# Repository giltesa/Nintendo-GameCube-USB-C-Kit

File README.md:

# Nintendo GameCube: USB-C Kit

The **Nintendo GameCube: USB-C Kit** is a board that allows to replace the original power connector for a modern and standard USB-C.

**If your original connector / power supply is too old or damaged** and you need a new one, or **if you would like to power up your Nintendo GameCube with a standard USB-C PD charger**, such as the charger for your phone, or laptop, you can do so with this kit.

## HOW DOES IT WORK?

The **USB-C Power Delivery technology (USB-C PD)** allows for communication between the device and the charger, enabling the negotiation of the voltage to be supplied through the USB-C cable. In this case, the microchip included in this board is configured to request 12V, signaling to the charger that it requires 12V to operate. If the charger is compatible, it will supply the requested voltage. If it’s not compatible, nothing will happen, and the Nintendo GameCube won’t be able to power on.

## Would you like it?

[**Nintendo GameCube: USB-C Kit**](https://shop.giltesa.com/?p=1995)

## License

This project is licensed under a **Creative Commons** license:
**[Attribution-NonCommercial-ShareAlike 4.0 International (CC BY-NC-SA 4.0) ](https://creativecommons.org/licenses/by-nc-sa/4.0/)**

Check the [LICENSE.md](LICENSE.md) for more information.

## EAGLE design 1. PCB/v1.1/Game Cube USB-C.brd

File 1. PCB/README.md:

# Source Code Availability Notice

The source code for the electronic circuits previously shared in this repository is **no longer publicly available**.

This decision has been made due to repeated misuse of the shared materials by third parties who have used the code to manufacture and sell products derived from this work for commercial gain, in violation of the license under which it was originally shared.

The original license explicitly **prohibits commercial use** of this work without proper authorization. Unfortunately, the terms of the license were not respected, which undermines the purpose of sharing the source code and the trust of the community.

Thank you for your understanding and respect for intellectual property rights.

## Unauthorized Sellers

The following vendors are listed here because they have **violated the project license** and are **illegally profiting** from the sale of counterfeit products without our authorization:

- Treasure Game Accessory Store

- Shop910920001 Store

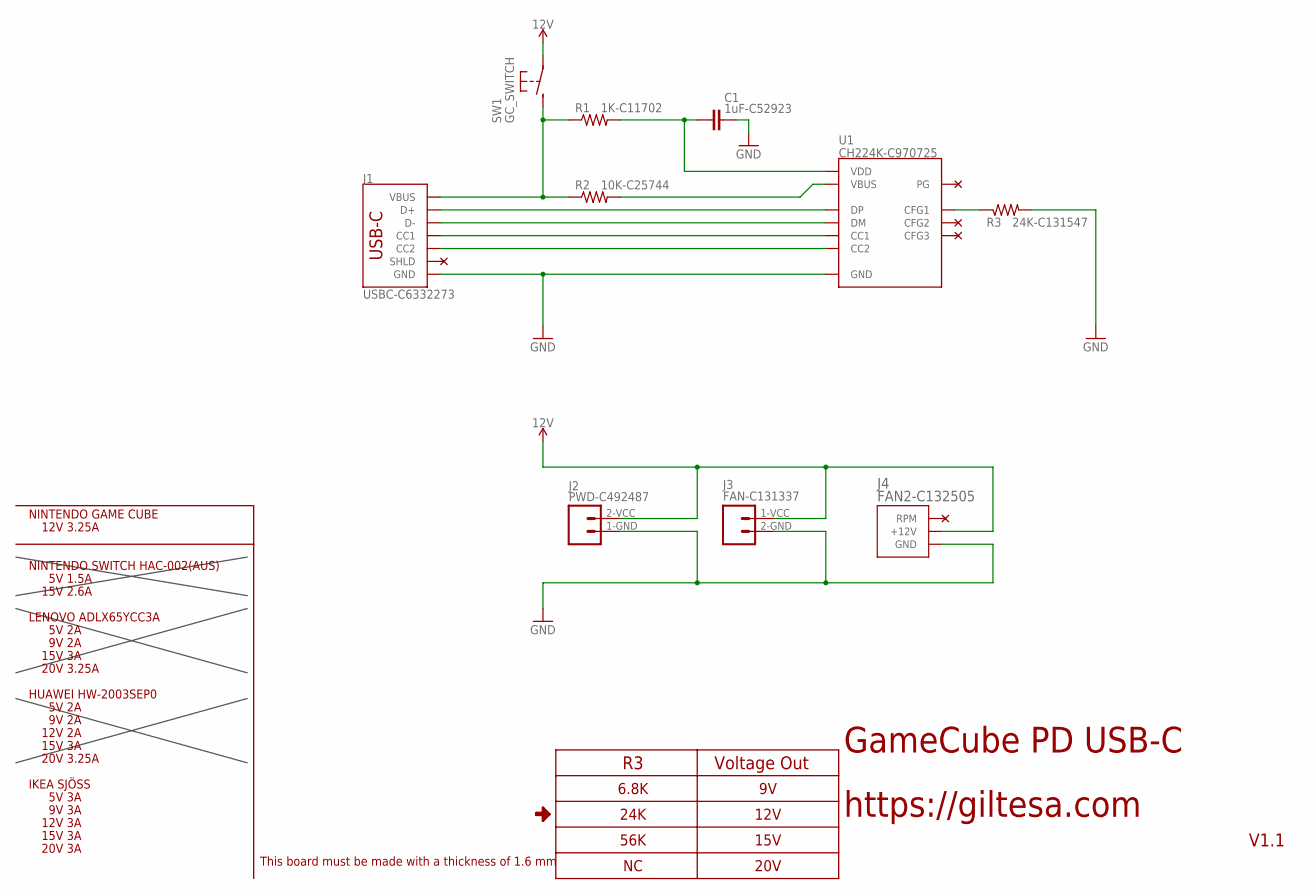
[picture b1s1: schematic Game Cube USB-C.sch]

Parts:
C1: 1uF-C52923; C0402_S
J1: USBC-C6332273; USB-C_16P_3MM
J2: PWD-C492487; GC_PWD_CONNECTOR
J3: FAN-C131337; GC_FAN_CONNECTOR
J4: FAN2-C132505; MOLEX-W-2510S03P
R1: 1K-C11702; R0402
R2: 10K-C25744; R0402
R3: 24K-C131547; R0402
SW1: GC_SWITCH
U1: CH224K-C970725; ESSOP10

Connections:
12V: J2.2-VCC (2), J3.1-VCC (1), J4.P2-12V (+12V), SW1.P$1 (1)
CC1: J1.A5-CC1 (CC1), U1.7 (CC1)
CC2: J1.B5-CC2 (CC2), U1.6 (CC2)
D+: J1.A6-DP1 (D+), J1.B6-DP2 (D+), U1.4 (DP)
D-: J1.A7-DN1 (D-), J1.B7-DN2 (D-), U1.5 (DM)
GND: C1.2, J1.GND1 (GND), J1.GND2 (GND), J2.1-GND (1), J3.2-GND (2), J4.P3-GND (GND), R3.2, U1.0 (GND)
unnamed: R3.1, U1.9 (CFG1)
unnamed: R2.2, U1.8 (VBUS)
VBUS: J1.VBUS1 (VBUS), J1.VBUS2 (VBUS), R1.1, R2.1, SW1.P$2 (2)
VDD: C1.1, R1.2, U1.1 (VDD)

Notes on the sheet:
GameCube PD USB-C
https://giltesa.com
V1.1
This board must be made with a thickness of 1.6 mm
NINTENDO SWITCH HAC-002(AUS)
5V 1.5A
15V 2.6A
HUAWEI HW-2003SEP0
5V 2A
9V 2A
12V 2A
15V 3A
20V 3.25A
NINTENDO GAME CUBE
12V 3.25A
Voltage Out
6.8K
24K
56K
12V
15V
20V
LENOVO ADLX65YCC3A
IKEA SJÖSS
5V 3A
9V 3A
12V 3A
20V 3A

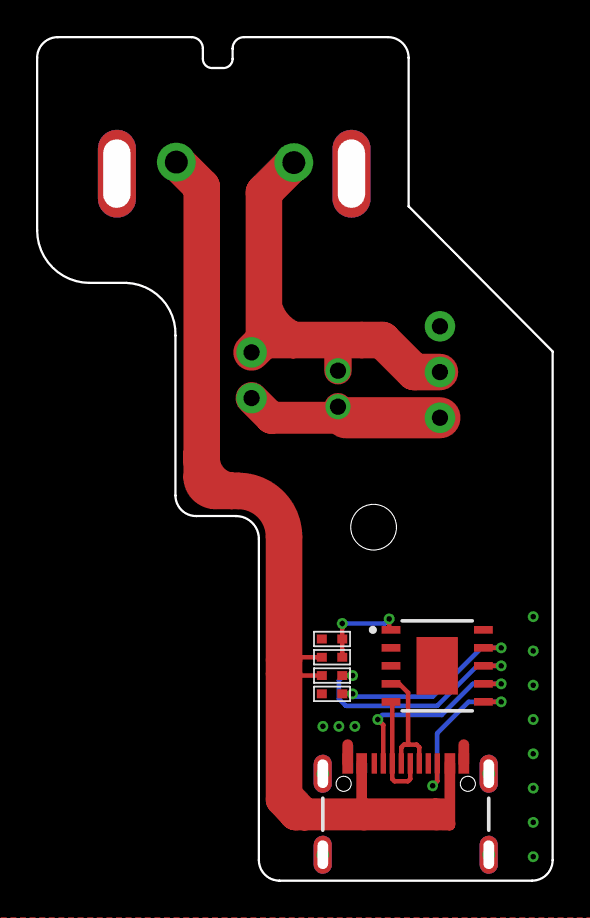
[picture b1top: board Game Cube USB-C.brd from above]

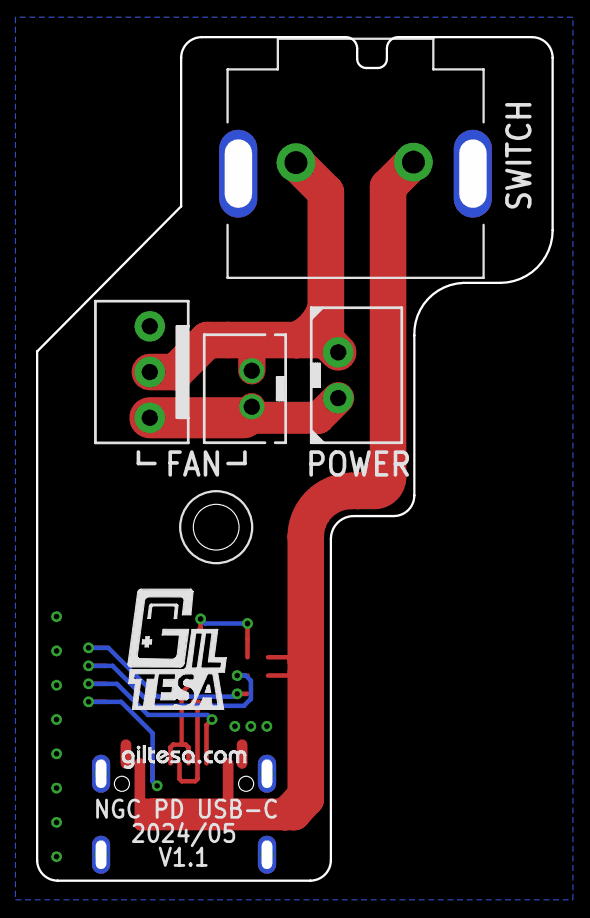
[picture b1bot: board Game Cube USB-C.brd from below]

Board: 2 copper layers, 28.6 x 46.9 mm, 13 parts (6 on the bottom side), 10 nets.

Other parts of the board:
U$6: GC_DRILL_SCREW
U$8: GILTESA_LOGO_MASK_7MM
U$28: GILTESA.COM_MASK_7MM

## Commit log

2024-03-24 no message
2024-10-10 v1.0
2024-10-10 v1.1

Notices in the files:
parts and their libraries:
COPYRIGHT: Copyright (C) 2024 Ultra Librarian. All rights reserved.
SparkFun: Licensing: CC v3.0 Share-Alike You are welcome to use this library for commercial purposes.
SparkFun-PowerSymbols: Licensing: Creative Commons ShareAlike 4.0 International - https://creativecommons.org/licenses/by-sa/4.0
